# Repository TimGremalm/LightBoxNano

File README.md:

# LightBoxNano
a generic LED controller that can be populated for either RGBW LED strip or addressable LED strip like WS2812.

It has the option for populating a pair of potentiometer, and a 5 way slider switch for controlling light modes.

An Arduino Nano is mounted using ordinary 2.54mm pitch pin headers.
Optionally a ESP32 Pico Kit can be mounted instead of the Nano, this is much more expensive it is a more powerful MCU and have WiFi.

A RS485 receiver and a pair of XLR connectors can also transform the LED controller into a DMX driver.

# Power Supply and voltage rails
## Input rail
The input voltage to LightBoxNano are called VIN and can range from 5 to 30V.
Make sure to only feed LightBoxNano with a voltage that the LED strip can handle. The maximum voltage is limited by the maximum voltage of the IRLML6344 Mosfets and of what the LED strip can handle.

If using 5V on Vin you need to read "Logic rail" to populate it correctly.

## RGBW rail
The positive rail for the LED strip driver is directly fed from VIN, it's usually 12V.

## Addressable rail
The positive rail for the addressable LED strip driver is directly fed from VIN, it's usually 5V.

## Logic rail
The logic rail should be 5V and feed the micro controller.

There is 2 options for the logic rail:
* Use buck, when Vin is greater than 5.5V.
* Use direct jumper link when Vin is 5V.

Note that the logic rail bypasses Vin_fused.

The buck converter using TI's guide:
https://webench.ti.com/power-designer/switching-regulator/select

https://webench.ti.com/appinfo/webench/scripts/SDP.cgi?ID=572687AF787DDED1

## Protection circuit
There is 2 options for input protection:
* A classic fuse
* Highside High Current Power Switch

### Classic Fuse
A much cheaper option then the high side switch, but one time use only.
Populate with a  appropriate 1206 fast blow fuse.
Example: Fuse Fast Blow 10A 1206 MCCFB1206TFF/10

No reverse polarity protection exist when using a classic fuse.

### Highside High Current Power Switch
The Infineon BTS50055-1TMC is a highside high current power switch with buildt in reverse
polarity and temperature protection.

It's also used to measure current consumption; Current_Feedback as analog output.
To enable the high power switch Enable_Vin_fused must be driven low.

Both Current_Feedback and Enable_Vin_fused goes to the MCU so it can act on over current
and act as a resettable fuse.

Vin_fused
| Channel			| Arduino Nano		| ESP32 |
| ----------------- | ----------------- | ----- |
| Current_Feedback	| A0 (PC0)			| IO38	|
| Enable_Vin_fused	| D13 (PB5)			| IO37	|

# RGBW driver
This is made for LED strip that have red, green, blue and white channels that have a common positive rail like +12V.
The LED driver can drive 4 output channels in constant voltage mode at 5A each. The channel can drive up to 10A current if an optional IRLML6344 is mounted.
One color channel on a 5m LED strip consisting of 300 LED's will draw 6A (20mA x 300px) when fully lit. A full RGB strip 18A, and a RGBW strip 24A.

| Channel	| Arduino Nano		| ESP32 |
| --------- | ----------------- | ----- |
| Red		| D5 (PD5)			| IO26	|
| Green		| D6 (PD6)			| IO27	|
| Blue		| D9 (PB1)			| IO13	|
| White		| D10 (PB2)			| IO15	|

# Addressable LED driver
Addressable LED strip is hooked up directly to VIN and the data pin is going to micro controller via a 1k resistor.

| Channel		| Arduino Nano		| ESP32 |
| ------------- | ----------------- | ----- |
| Addressable	| D3 (PD3)			| IO25	|

# Control interface
Two potentiometers can optionally be mounted. They are pulled up to 3.3V, so you won't get the full range on the Nano.
| Channel	| Arduino Nano		| ESP32 |
| --------- | ----------------- | ----- |
| POT_1		| A1 (PC1)			| IO26	|
| POT_2		| A2 (PC2)			| IO27	|

A 10 position rotary coded switch can optionally be mounted for selecting different modes.
| Channel	| Arduino Nano		| ESP32 |
| --------- | ----------------- | ----- |
| SwCode1	| D7 (PD7)			| IO14	|
| SwCode2	| D8 (PB0)			| IO12	|
| SwCode4	| D11 (PB3)			| IO2	|
| SwCode8	| D12 (PB4)			| IO4	|

10 position switch is coded in binary.
| Code	| 0	| 1	| 2	| 3	| 4	| 5	| 6	| 7	| 8	| 9	|
| ----- | -	| -	| -	| -	| -	| -	| -	| -	| -	| -	|
| 1		| 	| *	| 	| *	| 	| *	| 	| *	| 	| *	|
| 2		| 	| 	| *	| *	| 	| 	| *	| *	| 	| 	|
| 4		| 	| 	| 	| 	| *	| *	| *	| *	| 	| 	|
| 8		| 	| 	| 	| 	| 	| 	| 	| 	| *	| *	|

Also a pin header of the Arduino Nano will be easily assessable for hooking up random stuff.

# DMX Tranceiver
A RS-485 transceiver can optionally be mounted for sending and receiveing DMX512.
It uses ADM2687E which isolates the RS-485 bus from the low voltage micro controller side. This is important as electrical errors down the bus can propagage along the bus.
ADM2687E also isolates the power on the bus side by a buildt in DC to DC converter.

The tranceiver can be set to send DMX data if the jumper links "Link_DriverOutputA1" and "Link_DriverOutputB1" is soldered.

| Jumper							| Description													|
| --------------------------------- | -------------------------------------------------------------	|
| Link_DriverOutputA1				| Links the Z (Driver Inverting Output) to DMX+					|
| Link_DriverOutputB1				| Links the Y (Driver Noninverting Output) to DMX-				|
| Receiver_Disable1					| Pulls RE (Receiver Enable) to High which disables receiver	|
| Receiver_Enable1					| Pulls RE (Receiver Enable) to Low which enables receiver		|
| Driver_Enable1					| Pulls DE (Driver Enable) to High which enables sender			|
| Driver_Disable1					| Pulls DE (Driver Enable) to Low which disables sender			|
| Link_TransceiverGnd_To_DMXgnd1	| Links DMX bus Gnd to ADM2687E Gnd2							|
| Link_DMXgnd_To_DMXchassignd1		| Links DMX ground shield to ADM2687E Gnd2						|

DMX Send and Receive can be hooked up to UART channels on a MCU.
Receiver Enable and Driver Enable can also be driven by the micro controller (only ESP32).
| Channel			| Arduino Nano		| ESP32 |
| ----------------- | ----------------- | ----- |
| DMX_Send			| D1 TX (PD0)		| IO21	|
| DMX_Receive		| D0 RX (PD1)		| IO22	|
| DMX_ReceiveEnable	| N.C				| IO19	|
| DMX_DriveEnable	| N.C				| IO23	|

# MCU
An Arduino Nano V3 (ATmega328) is selected because it's cheap, available and have enough power for most applications.

Another option is to mount a ESP32 Pico Kit instead which is much more powerful and have built in WiFi.

# BOM (Bill Of Material)
| Amount	| Manufacturer		| Description										| Article Number		| URL																									|
| --------- | ----------------- | -------------------------------------------------	| --------------------- | ----------------------------------------------------------------------------------------------------- |
| 1			| Arduino			| MCU Arduino Nano 3 ATmega328						| A000005				| https://se.farnell.com/arduino-org/a000005/arduino-nano-utv-rd-kort/dp/1848691						|
| 1			| Espressif			| MCU ESP32 Pico Kit V4								| ESP32-PICO-KIT		| https://www.digikey.com/product-detail/en/espressif-systems/ESP32-PICO-KIT/1904-1030-ND/9381703		|
| 8			| Infineon			| Mosfet N-Ch 5A SOT-23								| IRLML6344TRPBF		| https://se.farnell.com/infineon/irlml6344trpbf/mosfet-n-kan-30v-5a-sot23/dp/1857299					|
| 1			| Infineon			| Highside High Current Power Switch 34V 17A 6.0 mΩ	| BTS500551TMCATMA1		| https://se.farnell.com/infineon/bts500551tmcatma1/effektbelastning-h-s-34v-to-220/dp/2480566			|
| 1			| Analog Devices	| RS485 Transceiver Isolated						| ADM2687EBRIZ			| https://se.farnell.com/analog-devices/adm2687ebriz/transceiver-iso-rs485-16soic/dp/2008784			|
| 1			| Multicomp			| Fuse Fast Blow 10A 1206							| MCCFB1206TFF/10		| https://se.farnell.com/multicomp/mccfb1206tff-10/s-kring-ytmont-10a-snabb-1206/dp/2850011				|
| 1			| Littelfuse		| Schottky 200V 10A									| MBRD10200CT			| https://se.farnell.com/littelfuse/mbrd10200ct/schottky-rect-200v-10a-to-252/dp/2773825				|
| 1			| Nexperia			| ESD protection diode 5V 1.55pF					| PESD5V0X1UAB,115		| https://se.farnell.com/nexperia/pesd5v0x1uab-115/diode-esd-low-capacitance-sod523/dp/2069370			|
| 1			| Vishay-Dale		| Inductor 47µH 42.7mΩ								| IHLP6767GZER470M11	| https://se.farnell.com/vishay/ihlp6767gzer470m11/inductor-47uh-8-6a-20/dp/1845598						|
| 1			| Texas Instruments	| Buck 5V 3A										| LM2596SX-5.0/NOPB		| https://se.farnell.com/texas-instruments/lm2596sx-5-0-nopb/dc-dc-conv-buck-150khz-to-263/dp/2781829	|
| 1			| Kingbright		| LED Red 20mA 0603									| KP-1608SURCK			| https://se.farnell.com/kingbright/kp-1608surck/led-red-80mcd-630nm-smd/dp/2449786						|
| 2			| Multicomp			| Cap 10nF 50V 0603									| MCU0603R103KCT		| https://se.farnell.com/multicomp/mcu0603r103kct/cap-0-01-f-50v-10-x7r-0603/dp/9406182RL				|
| 4			| Multicomp			| Cap 100nF 16V 0603								| MC0603B104J160CT		| https://se.farnell.com/multicomp/mc0603b104j160ct/cap-0-1-f-16v-5-x7r-0603/dp/2320813					|
| 1			| AVX				| Cap 4.7µF 10V 1.4Ω 1206 Solid Electrolyte			| TPSA475K010R1400		| https://se.farnell.com/avx/tpsa475k010r1400/cap-4-7-f-10v-10-1206-smd/dp/1135104						|
| 2			| Taiyo Yuden		| Cap 10µF 10V 0603									| LMK107BBJ106MALT		| https://se.farnell.com/taiyo-yuden/lmk107bbj106malt/cap-10-f-10v-20-x5r-0603/dp/2113070				|
| 1			| Panasonic			| Cap 18µF 50V 35mΩ Aluminium Electrolytic			| 50SVPF18M				| https://se.farnell.com/panasonic/50svpf18m/cap-18-f-50v-20-radial/dp/2354813							|
| 1			| Kemet				| Cap 100µF 50V 27mΩ Aluminium Electrolytic			| A767MU107M1HLAE027	| https://se.farnell.com/kemet/a767mu107m1hlae027/kond-alu-polymer-100-f-50v-rad/dp/2614195RL			|
| 1			| Knitter-Switch	| Rotary Coded Switch 10 Position					| DRR4010				| https://se.farnell.com/knitter-switch/drr4010/rotary-switch-pcb-bcd/dp/807620							|
| 2			| Alps Alpine		| Pot 10k Linear									| 29 0001				| https://se.farnell.com/alps/29-0001/potentiometer-10k-20-0-05w/dp/1191735								|
| 1			| Multicomp			| Resistor 120R 0603								| MC0100W06031120R		| https://se.farnell.com/multicomp/mc0100w06031120r/motst-tjockfilm-120r-1-0-063w/dp/2845766			|
| 1			| Multicomp			| Resistor 300R 0603								| MC0100W06031300R		| https://se.farnell.com/multicomp/mc0100w06031300r/motst-tjockfilm-300r-1-0-063w/dp/2845860			|
| 8			| Multicomp			| Resistor 1k 0603									| MC0100W060311K		| https://se.farnell.com/multicomp/mc0100w060311k/motst-tjockfilm-1k-1-0-063w-0603/dp/2845750			|
| 8			| Multicomp			| Resistor 10k 0603									| MC0100W0603110K		| https://se.farnell.com/multicomp/mc0100w0603110k/motst-tjockfilm-10k-1-0-063w-0603/dp/2845751			|
| 1			| Neutrik			| XLR 3-pole female Horizontal PCB mount			| NC3FAAH2				| https://se.farnell.com/neutrik/nc3faah2/socket-xlr-pcb-horizontal-3pole/dp/1310023					|
| 1			| Neutrik			| XLR 3-pole male Horizontal PCB mount				| NC3MAAH				| https://se.farnell.com/neutrik/nc3maah/plug-xlr-pcb-horizontal-3pole/dp/1310044						|
| 1			| Phoenix Contact	| Connector Male 2 pin MSTBA 2,5/ 2-G-5,08			| 1757242				| https://se.farnell.com/phoenix-contact/1757242/header-right-angle-5-08mm-2way/dp/3705171				|
| 1			| Phoenix Contact	| Connector Male 3 pin MSTBA 2,5/ 3-G-5,08			| 1757255				| https://se.farnell.com/phoenix-contact/1757255/connector-header-tht-ra-5-08mm/dp/3705183				|
| 1			| Phoenix Contact	| Connector Male 5 pin MSTBA 2,5/ 5-G-5,08			| 1757271				| https://se.farnell.com/phoenix-contact/1757271/header-right-angle-5-08mm-5way/dp/3705201				|
| 1			| Phoenix Contact	| Connector Female 2 pin MSTB 2,5/ 2-ST-5,08		| 1757019				| https://se.farnell.com/phoenix-contact/1757019/terminal-block-pluggable-2pos/dp/3705353				|
| 1			| Phoenix Contact	| Connector Female 3 pin MSTB 2,5/ 3-ST-5,08		| 1757022				| https://se.farnell.com/phoenix-contact/mstb2-5-3-st-5-08/terminal-block-pluggable-3pos/dp/3705365		|
| 1			| Phoenix Contact	| Connector Female 5 pin MSTB 2,5/ 5-ST-5,08		| 1757048				| https://se.farnell.com/phoenix-contact/1757048/terminal-block-pluggable-5pos/dp/3705389				|
| 1			| Multicomp			| Barrel Jack Switch 5A 2mm							| SPC21364				| https://se.farnell.com/multicomp/spc21364/connector-power/dp/1654842									|
| 1			| Multicomp			| Enclosure 120x120x60mm ABS IP65					| MC001076				| https://se.farnell.com/multicomp/mc001076/l-da-ip65-abs-gr-/dp/2544917								|

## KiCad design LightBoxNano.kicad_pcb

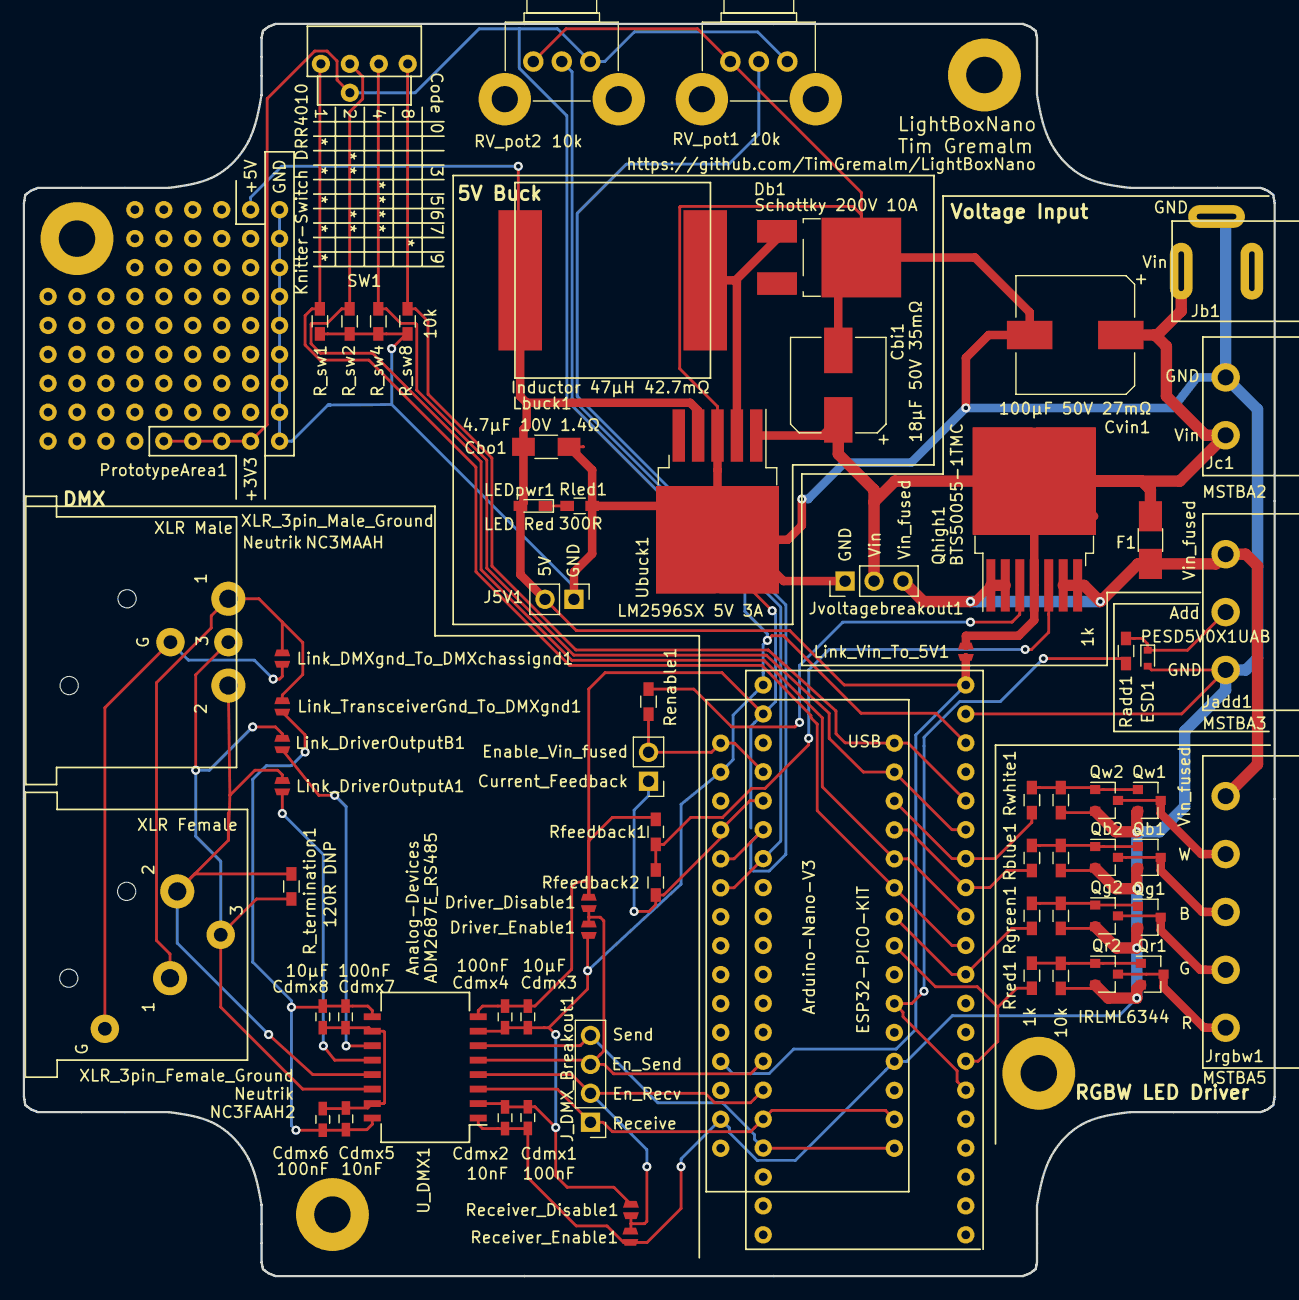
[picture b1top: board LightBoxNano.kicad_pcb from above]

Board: 2 copper layers, 109.8 x 109.9 mm, 74 parts (0 on the bottom side), 43 nets.

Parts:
Cbi1: 18µF 50V 35mΩ; CP_Elec_8x10
Cbo1: 4.7µF 10V 1.4Ω; C_1206_HandSoldering
Cdmx1, Cdmx4, Cdmx6, Cdmx7: 100nF; C_0603_HandSoldering
Cdmx2, Cdmx5: 10nF; C_0603_HandSoldering
Cdmx3, Cdmx8: 10µF; C_0603_HandSoldering
Cvin1: 100µF 50V 27mΩ; CP_Elec_10x10.5
Db1: Schottky 200V 10A; TO-252-2_Rectifier
Driver_Disable1: DriverEnable; JUMPER-SOLDER-SMD
Driver_Enable1: DriverEnable; JUMPER-SOLDER-SMD
ESD1: PESD5V0X1UAB; D_SOD-523
F1: Fuse DNP; Fuse_SMD1206_HandSoldering
H1, H2, H3, H4: MountingHole; MountingHole_3.2mm_M3_Pad
J5V1: Conn_02 DNP; Pin_Header_Straight_1x02_Pitch2.54mm
J_DMX_Breakout1: Conn_04; Pin_Header_Straight_1x04_Pitch2.54mm
Jadd1: MSTBA3; PhoenixContact-MSTBA_2,5_4-G-5,08_3pole
Jb1: Barrel Jack Switch 5A 2mm; BarrelJack_SPC21364
Jc1: MSTBA2; PhoenixContact-MSTBA_2,5_4-G-5,08_2pole
Jpowerswitchbreakout1: Conn_02 DNP; Pin_Header_Straight_1x02_Pitch2.54mm
Jrgbw1: MSTBA5; PhoenixContact-MSTBA_2,5_4-G-5,08_5pole
Jvoltagebreakout1: Conn_03 DNP; Pin_Header_Straight_1x03_Pitch2.54mm
LEDpwr1: LED Red; LED_0603_HandSoldering
Lbuck1: Inductor 47µH 42.7mΩ; Inductor_IHLP6767GZER470M11
Link_DMXgnd_To_DMXchassignd1: LinkDmxGndToChassiGnd; JUMPER-SOLDER-SMD
Link_DriverOutputA1: LinkDriverOutput; JUMPER-SOLDER-SMD
Link_DriverOutputB1: LinkDriverOutput; JUMPER-SOLDER-SMD
Link_TransceiverGnd_To_DMXgnd1: LinkTransceiverGndToDmxGnd; JUMPER-SOLDER-SMD
Link_Vin_To_5V1: Link Vin to 5V; JUMPER-SOLDER-SMD
MCU_esp1: ESP32-PICO-KIT; ESP32-PICO-KIT_Jumper
MCU_nano1: Arduino-Nano-V3; Arduino-Nano-V3_Jumper
PrototypeArea1: Conn_03; PrototypeArea
Qb1, Qb2: IRLML6344; SOT-23
Qg1, Qg2: IRLML6344; SOT-23
Qhigh1: BTS50055-1TMC; TO-263-7_TabPin4
Qr1, Qr2: IRLML6344; SOT-23
Qw1, Qw2: IRLML6344; SOT-23
RV_pot1, RV_pot2: 10k; Potentiometer_Alps_RK09K_Vertical
R_sw1, R_sw2, R_sw4, R_sw8: 10k; R_0603_HandSoldering
R_termination1: 120R DNP; R_0603_HandSoldering
Radd1: 1k; R_0603_HandSoldering
Rblue1: 1k; R_0603_HandSoldering
Rblue_pulldown1: 10k; R_0603_HandSoldering
Receiver_Disable1: ReveiverEnable; JUMPER-SOLDER-SMD
Receiver_Enable1: ReceiverEnable; JUMPER-SOLDER-SMD
Renable1: 1k; R_0603_HandSoldering
Rfeedback1, Rfeedback2: 1k; R_0603_HandSoldering
Rgreen1: 1k; R_0603_HandSoldering
Rgreen_pulldown1: 10k; R_0603_HandSoldering
Rled1: 300R; R_0603_HandSoldering
Rred1: 1k; R_0603_HandSoldering
Rred_pulldown1: 10k; R_0603_HandSoldering
Rwhite1: 1k; R_0603_HandSoldering
Rwhite_pulldown1: 10k; R_0603_HandSoldering
SW1: Knitter-Switch DRR4010; DRR4010
U_DMX1: Analog-Devices-ADM2687E_RS485; SOIC-16W_7.5x12.8mm_Pitch1.27mm
Ubuck1: LM2596SX 5V 3A; TO-263-5_TabPin3
XLR_Female1: XLR_3pin_Female_Ground; XLR_3pole-female_Horizontal_PCB_mount_NC3FAAH2
XLR_Male1: XLR_3pin_Male_Ground; XLR_3pole-male_Horizontal_PCB_mount_NC3MAAH

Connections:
+3V3: Cdmx1.2, Cdmx2.2, Cdmx3.1, Cdmx4.1, Driver_Enable1.2, MCU_esp1.J2_20, MCU_esp1.J3_18, MCU_nano1.17, PrototypeArea1.3, RV_pot1.1, RV_pot2.1, Receiver_Disable1.1, SW1.C, U_DMX1.2, U_DMX1.7
+5V: Cbo1.1, J5V1.2, LEDpwr1.2, Lbuck1.2, Link_Vin_To_5V1.2, MCU_esp1.J3_20, MCU_nano1.27, PrototypeArea1.2, Ubuck1.4
/Addressable: MCU_esp1.J3_6, MCU_nano1.6, Radd1.2
/Current_Feedback: Jpowerswitchbreakout1.1, MCU_esp1.J2_16, MCU_nano1.19, Rfeedback2.2
/DMX512/DMX+: Link_DriverOutputB1.2, R_termination1.2, U_DMX1.14, XLR_Female1.3, XLR_Male1.3
/DMX512/DMX-: Link_DriverOutputA1.2, R_termination1.1, U_DMX1.13, XLR_Female1.2, XLR_Male1.2
/DMX512/DMXTransmitterY: Link_DriverOutputB1.1, U_DMX1.11
/DMX512/DMXTransmitterZ: Link_DriverOutputA1.1, U_DMX1.12
/DMX512/DMXchassignd: Link_DMXgnd_To_DMXchassignd1.2, XLR_Female1.G, XLR_Male1.G
/DMX512/DMXgnd: Link_DMXgnd_To_DMXchassignd1.1, Link_TransceiverGnd_To_DMXgnd1.2, XLR_Female1.1, XLR_Male1.1
/DMX512/GND2: Cdmx5.1, Cdmx6.1, Cdmx7.2, Cdmx8.2, Link_TransceiverGnd_To_DMXgnd1.1, U_DMX1.9, U_DMX1.16
/DMX_Enable_Receive: J_DMX_Breakout1.2, MCU_esp1.J2_6, Receiver_Disable1.2, Receiver_Enable1.2, U_DMX1.4
/DMX_Enable_Send: Driver_Disable1.1, Driver_Enable1.1, J_DMX_Breakout1.3, MCU_esp1.J2_7, U_DMX1.5
/DMX_Receive: J_DMX_Breakout1.1, MCU_esp1.J2_5, MCU_nano1.2, U_DMX1.3
/DMX_Send: J_DMX_Breakout1.4, MCU_esp1.J2_4, MCU_nano1.1, U_DMX1.6
/Enable_Vin_fused: Jpowerswitchbreakout1.2, MCU_esp1.J2_17, MCU_nano1.16, Renable1.1
/Gate_blue: MCU_esp1.J3_13, MCU_nano1.12, Rblue1.1
/Gate_green: MCU_esp1.J3_10, MCU_nano1.9, Rgreen1.1
/Gate_red: MCU_esp1.J3_7, MCU_nano1.8, Rred1.1
/Gate_white: MCU_esp1.J3_14, MCU_nano1.13, Rwhite1.1
/POT_1: MCU_esp1.J2_15, MCU_nano1.20, RV_pot1.2
/POT_2: MCU_esp1.J2_14, MCU_nano1.21, RV_pot2.2
/SwCode1: MCU_esp1.J3_11, MCU_nano1.10, R_sw1.2, SW1.1
/SwCode2: MCU_esp1.J3_12, MCU_nano1.11, R_sw2.2, SW1.2
/SwCode4: MCU_esp1.J3_15, MCU_nano1.14, R_sw4.2, SW1.4
/SwCode8: MCU_esp1.J3_16, MCU_nano1.15, R_sw8.2, SW1.8
/Vin: Cbi1.1, Cvin1.1, F1.2, Jb1.1, Jc1.1, Jvoltagebreakout1.2, Link_Vin_To_5V1.1, Qhigh1.4, Ubuck1.1
/Vin_fused: F1.1, Jadd1.3, Jrgbw1.5, Jvoltagebreakout1.3, Qhigh1.1, Qhigh1.2, Qhigh1.6, Qhigh1.7
GND: Cbi1.2, Cbo1.2, Cdmx1.1, Cdmx2.1, Cdmx3.2, Cdmx4.2, Cvin1.2, Db1.2, Driver_Disable1.2, ESD1.2, J5V1.1, Jadd1.1, Jb1.2, Jc1.2, Jvoltagebreakout1.1, MCU_esp1.J2_19, MCU_esp1.J3_19, MCU_nano1.4, MCU_nano1.29, PrototypeArea1.1, Qb1.2, Qb2.2, Qg1.2, Qg2.2, Qr1.2, Qr2.2, Qw1.2, Qw2.2, RV_pot1.3, RV_pot2.3, R_sw1.1, R_sw2.1, R_sw4.1, R_sw8.1, Rblue_pulldown1.2, Receiver_Enable1.1, Rfeedback1.2, Rgreen_pulldown1.2, Rled1.2, Rred_pulldown1.2, Rwhite_pulldown1.2, U_DMX1.1, U_DMX1.8, Ubuck1.3
unnamed: Cdmx5.2, Cdmx6.2, Cdmx7.1, Cdmx8.1, U_DMX1.10, U_DMX1.15
unnamed: Db1.1, Lbuck1.1, Ubuck1.2
unnamed: ESD1.1, Jadd1.2, Radd1.1
unnamed: Jrgbw1.1, Qr1.3, Qr2.3
unnamed: Jrgbw1.2, Qg1.3, Qg2.3
unnamed: Jrgbw1.3, Qb1.3, Qb2.3
unnamed: Jrgbw1.4, Qw1.3, Qw2.3
unnamed: LEDpwr1.1, Rled1.1
unnamed: Qb1.1, Qb2.1, Rblue1.2, Rblue_pulldown1.1
unnamed: Qg1.1, Qg2.1, Rgreen1.2, Rgreen_pulldown1.1
unnamed: Qhigh1.3, Renable1.2
unnamed: Qhigh1.5, Rfeedback1.1, Rfeedback2.1
unnamed: Qr1.1, Qr2.1, Rred1.2, Rred_pulldown1.1
unnamed: Qw1.1, Qw2.1, Rwhite1.2, Rwhite_pulldown1.1

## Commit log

2019-11-28 Schema Arduino Nano, Pots, Connectors
2019-11-28 Datasheet for Arduino Nano, Pots, Connectors
2019-11-28 Submodule kicad symbols and footprints
2019-11-28 Changed schema lib to submodule
2019-11-28 Update datasheets for Phoenix Contact
2019-11-28 Added BOM to readme
2019-11-28 Cleaned up readme
2019-11-28 BOM added N-channel mosfet IRLML6344
2019-11-28 Datasheet for IRLML6344 N-Channel mosfet
2019-11-29 Gitignore KiCad files
2019-11-29 Test to import on KiCad 5.1.5 on Windows 10
2019-11-29 Rough movement in schema
2019-11-29 Included sym-lib-table
2019-11-29 Added project symbol IRLML6344 N-channel mosfet
2019-11-29 Removed alias for symbol IRLML6344
2019-11-29 Grandious plans, and specs added in README
2019-11-29 Schema added 5V buck, Wemos D1 ESP8266, Structure
2019-11-29 Add resistor divider for POT connected to ESP8266
2019-11-29 Added RGBW LED driver to schema
2019-11-29 Added 5-way position switch
2019-11-29 Added DMX block to schema
2019-11-29 Footprint and datasheets for components in buck
2019-11-29 Footprint 0603 for resistors
2019-11-30 Datasheet for resistors in schema
2019-11-30 Automatic annotation
2019-11-30 Removed submodule KiCad libs, it's included in V5
2019-11-30 Footprint for Barrel Jack Connector
2019-11-30 Added link to IRLML6344 Mosfet's in schema
2019-11-30 Readme spelling and structure
2019-11-30 Change BOM link to IRLML6344 to a non reel
2019-11-30 Links and info about MCU's
2019-11-30 WeMos D1 to BOM
2019-11-30 PDF plot of schema
2019-11-30 Update BOM
2019-11-30 Schema details
2019-11-30 PDF plot
2019-12-02 Added adressable and RGBW to MCU nano
2020-04-02 ESP32-PICO-KIT V4 Footprint and Symbol
2020-04-02 Arduino Nano V3 Footprint and Symbol
2020-04-02 Switched out ESP8266 for ESP32
2020-04-02 Schema connect ESP32
2020-04-02 Symbol Arduino Label Placement
2020-04-02 Symbol ESP32 Solid Box
2020-04-02 Schema smaller connection placement
2020-04-02 Place Power on top and bottom in MCU symbol block
2020-04-02 Add PhoenixContact footprints, and set in schema
2020-04-03 Added DMX support via ADM2687E RS-485 Transiever
2020-04-03 Added older 2.3 datasheet for Arduino Nano
2020-04-03 Add XLR connectors Amphenol AC3FAH
2020-04-03 Switched XLR to Neutrik-NC3FAAH2
2020-04-04 Footprint Neutrik XLR NC3FAAH2 NC3MAAH
2020-04-04 Switched Pots to Alps 29 0001
2020-04-04 Added Rotary Code Knitter-Switch DRR4010
2020-04-05 Schema sub sheet for DMX512 and description texts
2020-04-05 Readme Control Interface
2020-04-05 Schema Cleanup
2020-04-06 Update Capacitors for the RS-485 transceiver
2020-04-06 Add power flags to outputs, fix validation errors
2020-04-06 Set correct footprint on caps belonging to ADM268
2020-04-06 Rough PCB layout
2020-04-06 Nicer placment of labels and components on PCB
2020-04-06 Add 3mm mounting holes
2020-04-06 Add sub sheet for Input Protection
2020-04-07 Add Input Protection, highside power switch, fuse
2020-04-07 Add Input Protection to PCB
2020-04-07 5V direct jumper link option for logic rail
2020-04-08 Input Protection description, Pwer Switch Feedback
2020-04-08 Adjust PCB size to enclosure
2020-04-08 Start routing on PCB
2020-04-08 Route PCB
2020-04-08 Add labels to PCB, plot output
2020-04-10 Pretty labels on PCB
2020-04-10 Smaller changes to labels on PCB
2020-04-10 Add solder prototype Area to PCB
2020-04-13 Add ESD protection diode
2020-04-13 Add Led Alert logotype, layout

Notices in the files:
LightBoxNano.kicad_pcb:
GPL 3.0
